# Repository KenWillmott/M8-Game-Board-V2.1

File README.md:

# M8-Game-Board-V2.1
Audio Video Joystick card for M8 bus

This board replaces the first game board, which was not fully working or fully M8 compatible.

It has a TMS9918A video processor with composite video output, stereo sound output from a Philips SAA1099 IC, and one Atari style joystick port. The sound IC and joystick are interfaced via an MC6821 PIA.

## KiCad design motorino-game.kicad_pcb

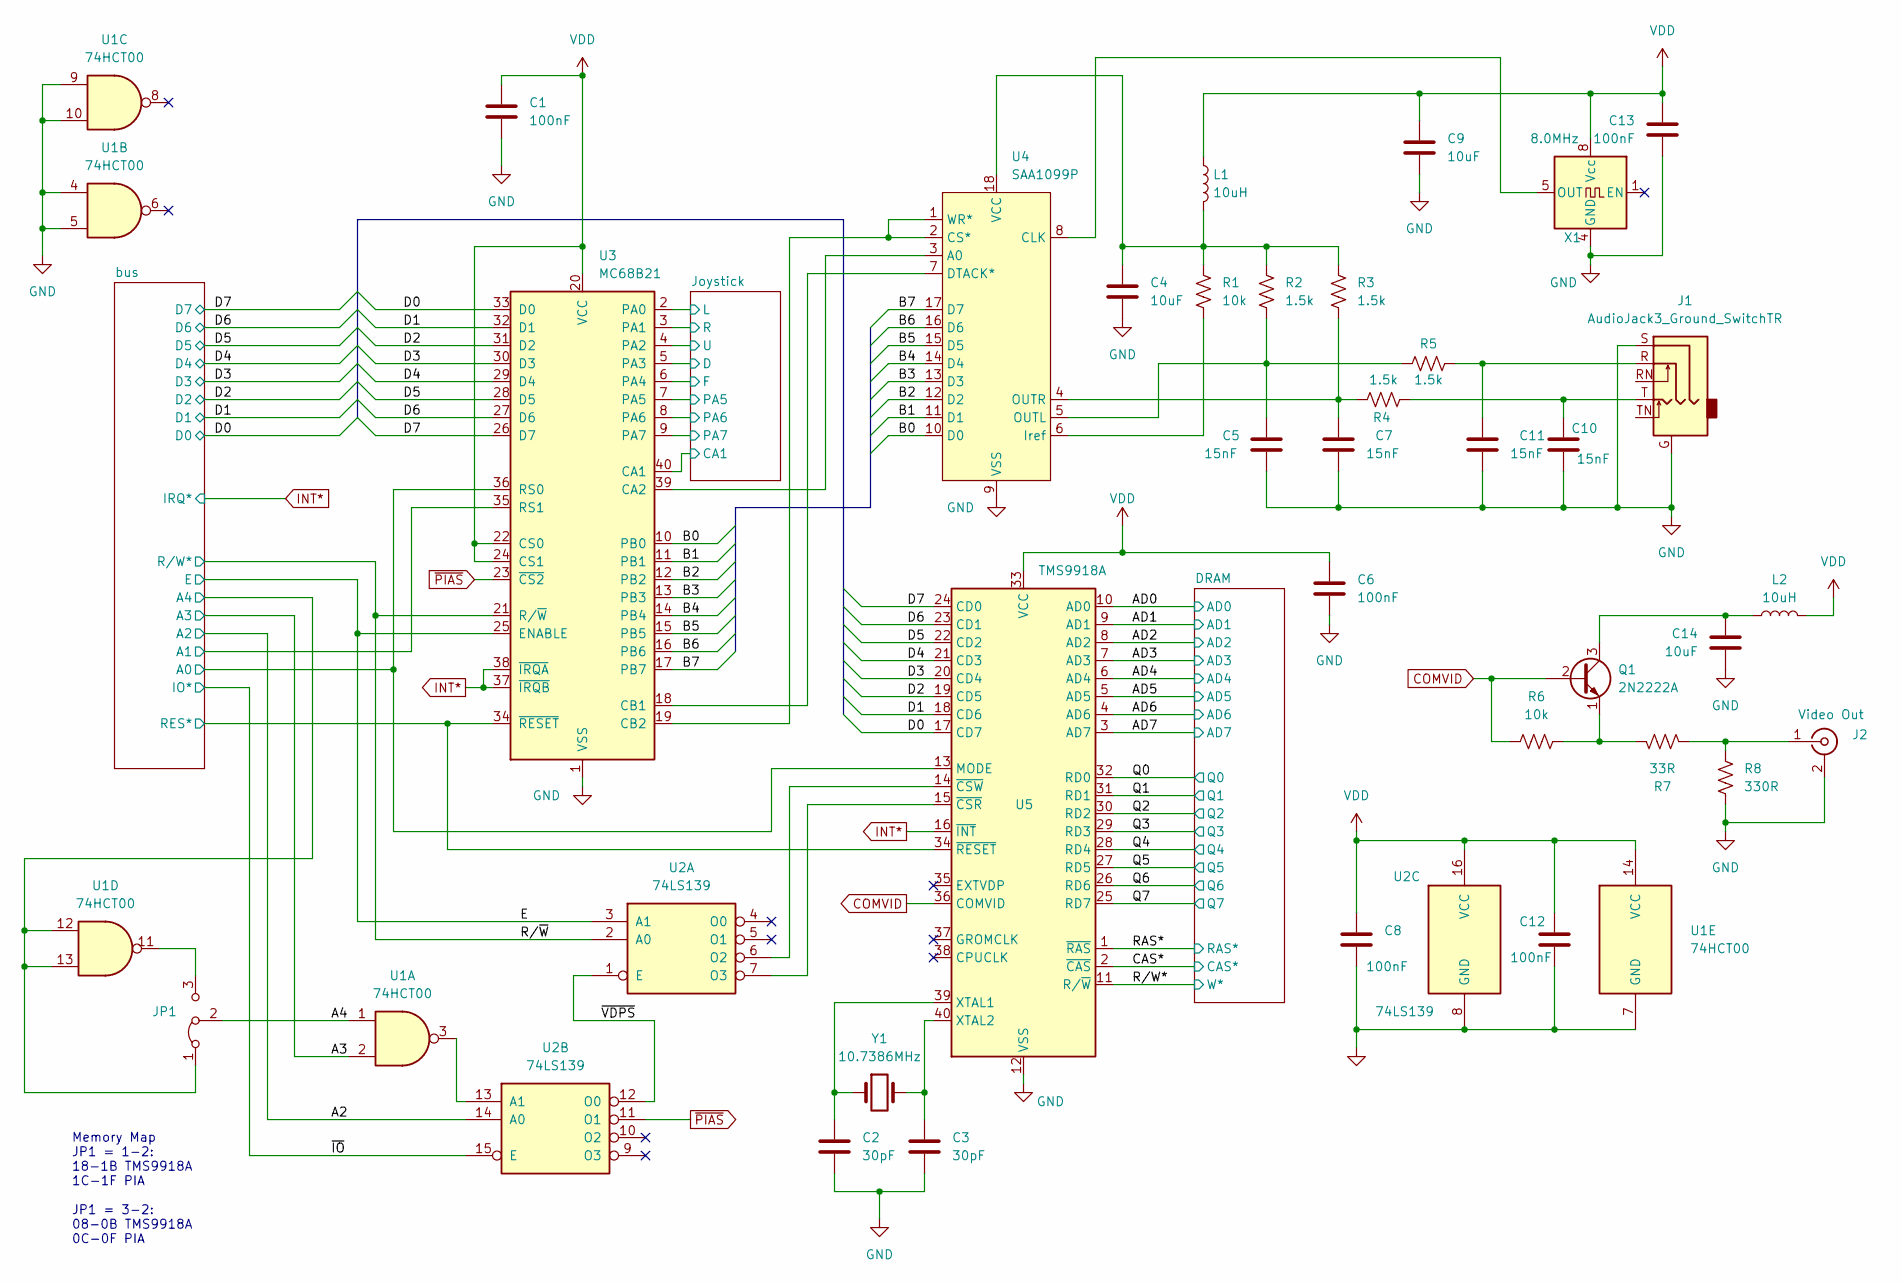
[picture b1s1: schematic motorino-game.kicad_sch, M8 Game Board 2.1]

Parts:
C1, C6, C8, C12, C13: 100nF; C_Disc_D5.0mm_W2.5mm_P5.00mm
C2, C3: 30pF; C_Disc_D5.0mm_W2.5mm_P5.00mm
C4, C9, C14: 10uF; C_Disc_D5.0mm_W2.5mm_P5.00mm
C5, C7, C10, C11: 15nF; C_Disc_D5.0mm_W2.5mm_P5.00mm
J1: AudioJack3_Ground_SwitchTR; Jack_3.5mm_CUI_SJ3-350113A-SMT_Horizontal
J2: Video Out; RCA jack
JP1: Jumper_3_Bridged12; PinHeader_1x03_P2.54mm_Vertical
L1, L2: 10uH; R_Axial_DIN0207_L6.3mm_D2.5mm_P10.16mm_Horizontal
Q1: 2N2222A; TO-92_Inline_Wide
R1, R6: 10k; R_Axial_DIN0207_L6.3mm_D2.5mm_P10.16mm_Horizontal
R2, R3, R4, R5: 1.5k; R_Axial_DIN0207_L6.3mm_D2.5mm_P10.16mm_Horizontal
R7: 33R; R_Axial_DIN0207_L6.3mm_D2.5mm_P10.16mm_Horizontal
R8: 330R; R_Axial_DIN0207_L6.3mm_D2.5mm_P10.16mm_Horizontal
U1: 74HCT00; DIP-14_W7.62mm_LongPads
U2: 74LS139; DIP-16_W7.62mm_LongPads
U3: MC68B21; DIP-40_W15.24mm
U4: SAA1099P; DIP-18_W7.62mm_LongPads
U5: TMS9918A; DIP-40_W15.24mm_LongPads
X1: 8.0MHz; Oscillator_DIP-8
Y1: 10.7386MHz; Crystal_HC49-U_Vertical

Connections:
/A2: U2.14 (A0); also elsewhere on the board
/A3: U1.2; also elsewhere on the board
/A4: JP1.2 (C), U1.1
/AD0: U5.10 (AD0); also elsewhere on the board
/AD1: U5.9 (AD1); also elsewhere on the board
/AD2: U5.8 (AD2); also elsewhere on the board
/AD3: U5.7 (AD3); also elsewhere on the board
/AD4: U5.6 (AD4); also elsewhere on the board
/AD5: U5.5 (AD5); also elsewhere on the board
/AD6: U5.4 (AD6); also elsewhere on the board
/AD7: U5.3 (AD7); also elsewhere on the board
/B0: U3.10 (PB0), U4.10 (D0)
/B1: U3.11 (PB1), U4.11 (D1)
/B2: U3.12 (PB2), U4.12 (D2)
/B3: U3.13 (PB3), U4.13 (D3)
/B4: U3.14 (PB4), U4.14 (D4)
/B5: U3.15 (PB5), U4.15 (D5)
/B6: U3.16 (PB6), U4.16 (D6)
/B7: U3.17 (PB7), U4.17 (D7)
/CAS*: U5.2 (~CAS); also elsewhere on the board
/D0: U3.33 (D0), U5.17 (CD7); also elsewhere on the board
/D1: U3.32 (D1), U5.18 (CD6); also elsewhere on the board
/D2: U3.31 (D2), U5.19 (CD5); also elsewhere on the board
/D3: U3.30 (D3), U5.20 (CD4); also elsewhere on the board
/D4: U3.29 (D4), U5.21 (CD3); also elsewhere on the board
/D5: U3.28 (D5), U5.22 (CD2); also elsewhere on the board
/D6: U3.27 (D6), U5.23 (CD1); also elsewhere on the board
/D7: U3.26 (D7), U5.24 (CD0); also elsewhere on the board
/E: U2.3 (A1), U3.25 (ENABLE); also elsewhere on the board
/Joystick/CA1: U3.40 (CA1); also elsewhere on the board
/Joystick/D: U3.5 (PA3); also elsewhere on the board
/Joystick/F: U3.6 (PA4); also elsewhere on the board
/Joystick/L: U3.2 (PA0); also elsewhere on the board
/Joystick/PA5: U3.7 (PA5); also elsewhere on the board
/Joystick/PA6: U3.8 (PA6); also elsewhere on the board
/Joystick/PA7: U3.9 (PA7); also elsewhere on the board
/Joystick/R: U3.3 (PA1); also elsewhere on the board
/Joystick/U: U3.4 (PA2); also elsewhere on the board
/Q0: U5.32 (RD0); also elsewhere on the board
/Q1: U5.31 (RD1); also elsewhere on the board
/Q2: U5.30 (RD2); also elsewhere on the board
/Q3: U5.29 (RD3); also elsewhere on the board
/Q4: U5.28 (RD4); also elsewhere on the board
/Q5: U5.27 (RD5); also elsewhere on the board
/Q6: U5.26 (RD6); also elsewhere on the board
/Q7: U5.25 (RD7); also elsewhere on the board
/RAS*: U5.1 (~RAS); also elsewhere on the board
/R/W*: U5.11 (R/~W); also elsewhere on the board
/R/~W: U2.2 (A0), U3.21 (R/~W); also elsewhere on the board
/bus/A0: U3.36 (RS0), U5.13 (MODE); also elsewhere on the board
/bus/A1: U3.35 (RS1); also elsewhere on the board
/bus/A4: JP1.1 (A), U1.12, U1.13; also elsewhere on the board
/bus/RES: U3.34 (~RESET), U5.34 (~RESET); also elsewhere on the board
/~IO: U2.15 (E); also elsewhere on the board
/~VDPS: U2.1 (E), U2.12 (O0)
COMVID: Q1.2 (B), R6.1, U5.36 (COMVID)
GND: C1.2, C2.2, C3.2, C4.2, C5.2, C6.2, C7.2, C8.2, C9.2, C10.2, C11.2, C12.2, C13.2, C14.2, J1.G, J1.S, J2.2 (Ext), R8.2, U1.4, U1.5, U1.7 (GND), U1.9, U1.10, U2.8 (GND), U3.1 (VSS), U4.9 (VSS), U5.12 (VSS), X1.4 (GND); also elsewhere on the board
INT*: U3.37 (~IRQB), U3.38 (~IRQA), U5.16 (~INT); also elsewhere on the board
unnamed: C10.1, J1.T, R4.1
unnamed: C11.1, J1.R, R5.1
unnamed: J2.1 (In), R7.1, R8.1
unnamed: JP1.3 (B), U1.11
unnamed: C14.1, L2.2, Q1.3 (C)
unnamed: Q1.1 (E), R6.2, R7.2
unnamed: U2.6 (O2), U5.14 (~CSW)
unnamed: U2.7 (O3), U5.15 (~CSR)
unnamed: U1.3, U2.13 (A1)
unnamed: U3.39 (CA2), U4.3 (A0)
unnamed: U3.18 (CB1), U4.7 (DTACK*)
unnamed: U3.19 (CB2), U4.1 (WR*), U4.2 (CS*)
unnamed: U4.8 (CLK), X1.5 (OUT)
unnamed: R1.2, U4.6 (Iref)
unnamed: C5.1, R2.2, R5.2, U4.5 (OUTL)
unnamed: C7.1, R3.2, R4.2, U4.4 (OUTR)
unnamed: C4.1, L1.2, R1.1, R2.1, R3.1, U4.18 (VCC)
unnamed: C2.1, U5.39 (XTAL1), Y1.1
unnamed: C3.1, U5.40 (XTAL2), Y1.2
VDD: C1.1, C6.1, C8.1, C9.1, C12.1, C13.1, L1.1, L2.1, U1.14 (VCC), U2.16 (VCC), U3.20 (VCC), U3.22 (CS0), U3.24 (CS1), U5.33 (VCC), X1.8 (Vcc); also elsewhere on the board
~PIAS: U2.11 (O1), U3.23 (~CS2)

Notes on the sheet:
Memory Map JP1 = 1-2: 18-1B TMS9918A 1C-1F PIA JP1 = 3-2: 08-0B TMS9918A 0C-0F PIA

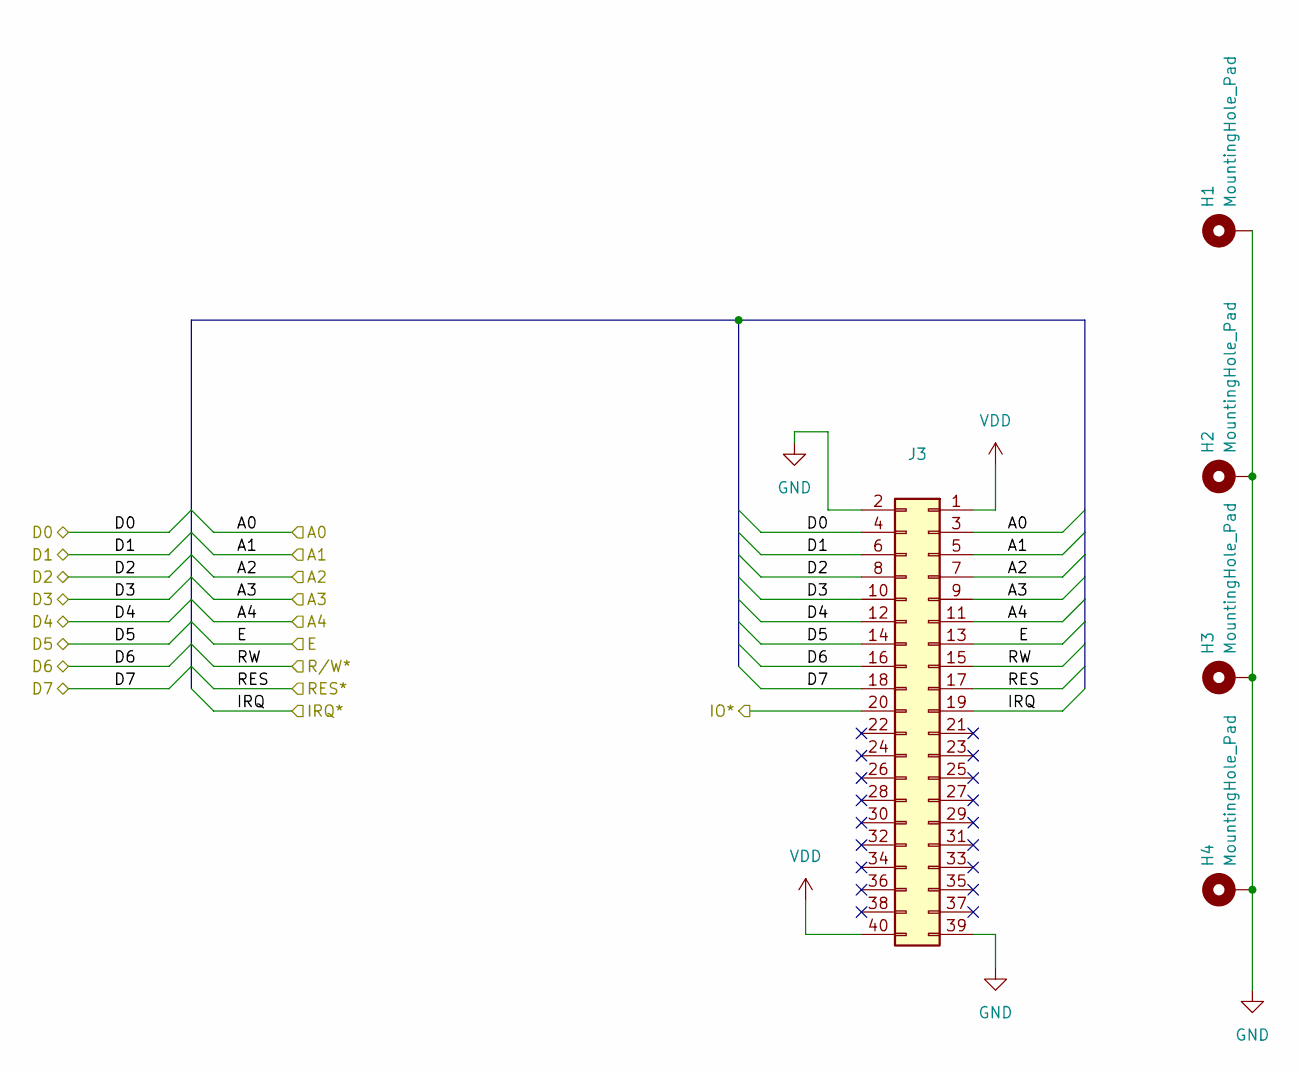
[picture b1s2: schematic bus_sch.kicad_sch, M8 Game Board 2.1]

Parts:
H1, H2, H3, H4: MountingHole_Pad; MountingHole_3.2mm_M3_Pad
J3: Conn_02x20_Odd_Even; PinHeader_2x20_P2.54mm_Vertical

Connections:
/A2: J3.7; also elsewhere on the board
/A3: J3.9; also elsewhere on the board
/D0: J3.4; also elsewhere on the board
/D1: J3.6; also elsewhere on the board
/D2: J3.8; also elsewhere on the board
/D3: J3.10; also elsewhere on the board
/D4: J3.12; also elsewhere on the board
/D5: J3.14; also elsewhere on the board
/D6: J3.16; also elsewhere on the board
/D7: J3.18; also elsewhere on the board
/E: J3.13; also elsewhere on the board
/R/~W: J3.15; also elsewhere on the board
/bus/A0: J3.3; also elsewhere on the board
/bus/A1: J3.5; also elsewhere on the board
/bus/A4: J3.11; also elsewhere on the board
/bus/RES: J3.17; also elsewhere on the board
/~IO: J3.20; also elsewhere on the board
GND: H1.1, H2.1, H3.1, H4.1, J3.2, J3.39; also elsewhere on the board
INT*: J3.19; also elsewhere on the board
VDD: J3.1, J3.40; also elsewhere on the board

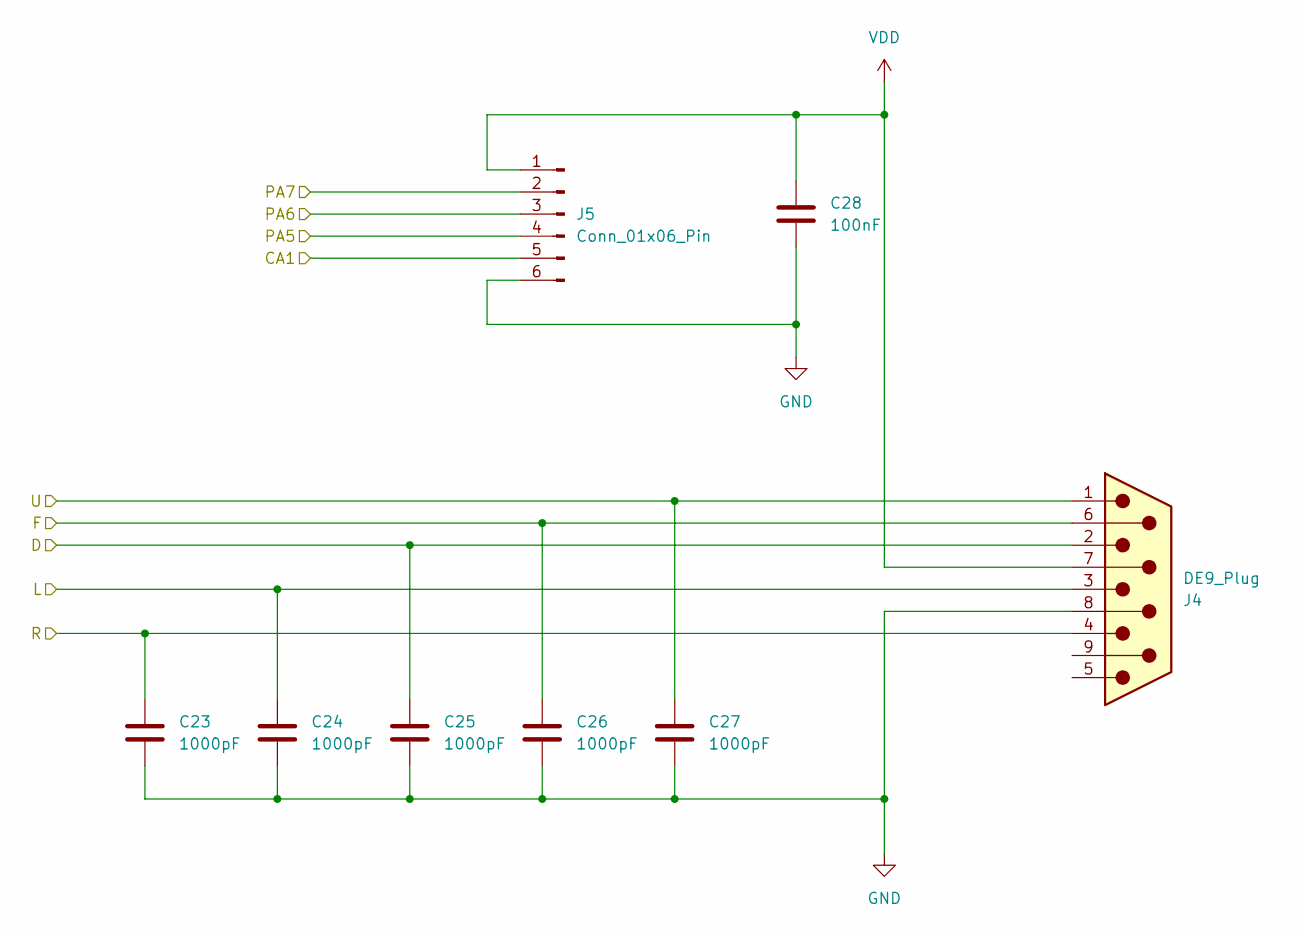
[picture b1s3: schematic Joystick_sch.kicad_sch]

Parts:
C23, C24, C25, C26, C27: 1000pF; C_Disc_D5.0mm_W2.5mm_P5.00mm
C28: 100nF; C_Disc_D5.0mm_W2.5mm_P5.00mm
J4: DE9_Plug; DSUB-9_Male_Horizontal_P2.77x2.84mm_EdgePinOffset9.90mm_Hou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
J5: Conn_01x06_Pin; PinHeader_1x06_P2.54mm_Vertical

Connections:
/Joystick/CA1: J5.5; also elsewhere on the board
/Joystick/D: C25.1, J4.2; also elsewhere on the board
/Joystick/F: C26.1, J4.6; also elsewhere on the board
/Joystick/L: C24.1, J4.3; also elsewhere on the board
/Joystick/PA5: J5.4; also elsewhere on the board
/Joystick/PA6: J5.3; also elsewhere on the board
/Joystick/PA7: J5.2; also elsewhere on the board
/Joystick/R: C23.1, J4.4; also elsewhere on the board
/Joystick/U: C27.1, J4.1; also elsewhere on the board
GND: C23.2, C24.2, C25.2, C26.2, C27.2, C28.2, J4.8, J5.6; also elsewhere on the board
VDD: C28.1, J4.7, J5.1; also elsewhere on the board

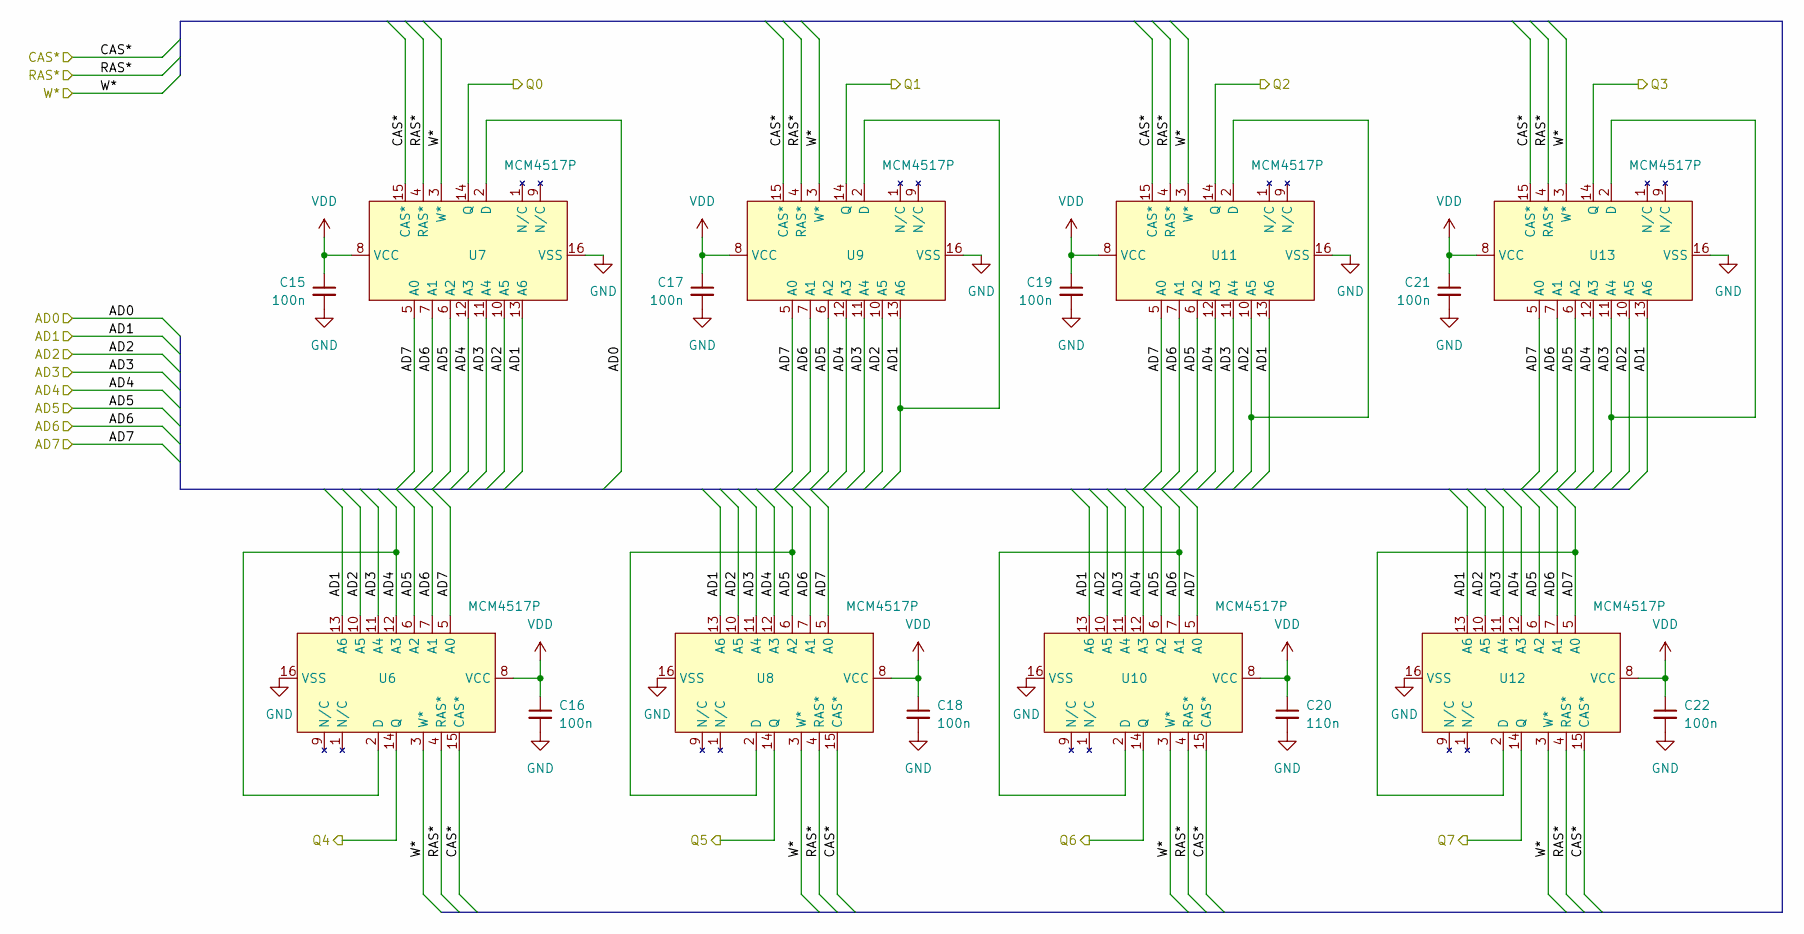
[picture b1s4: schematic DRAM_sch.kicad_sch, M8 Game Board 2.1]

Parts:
C15, C16, C17, C18, C19, C21, C22: 100n; C_Disc_D5.0mm_W2.5mm_P5.00mm
C20: 110n; C_Disc_D5.0mm_W2.5mm_P5.00mm
U6, U7, U8, U9, U10, U11, U12, U13: MCM4517P; DIP-16_W7.62mm_LongPads

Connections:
/AD0: U7.2 (D); also elsewhere on the board
/AD1: U6.13 (A6), U7.13 (A6), U8.13 (A6), U9.2 (D), U9.13 (A6), U10.13 (A6), U11.13 (A6), U12.13 (A6), U13.13 (A6); also elsewhere on the board
/AD2: U6.10 (A5), U7.10 (A5), U8.10 (A5), U9.10 (A5), U10.10 (A5), U11.2 (D), U11.10 (A5), U12.10 (A5), U13.10 (A5); also elsewhere on the board
/AD3: U6.11 (A4), U7.11 (A4), U8.11 (A4), U9.11 (A4), U10.11 (A4), U11.11 (A4), U12.11 (A4), U13.2 (D), U13.11 (A4); also elsewhere on the board
/AD4: U6.2 (D), U6.12 (A3), U7.12 (A3), U8.12 (A3), U9.12 (A3), U10.12 (A3), U11.12 (A3), U12.12 (A3), U13.12 (A3); also elsewhere on the board
/AD5: U6.6 (A2), U7.6 (A2), U8.2 (D), U8.6 (A2), U9.6 (A2), U10.6 (A2), U11.6 (A2), U12.6 (A2), U13.6 (A2); also elsewhere on the board
/AD6: U6.7 (A1), U7.7 (A1), U8.7 (A1), U9.7 (A1), U10.2 (D), U10.7 (A1), U11.7 (A1), U12.7 (A1), U13.7 (A1); also elsewhere on the board
/AD7: U6.5 (A0), U7.5 (A0), U8.5 (A0), U9.5 (A0), U10.5 (A0), U11.5 (A0), U12.2 (D), U12.5 (A0), U13.5 (A0); also elsewhere on the board
/CAS*: U6.15 (CAS*), U7.15 (CAS*), U8.15 (CAS*), U9.15 (CAS*), U10.15 (CAS*), U11.15 (CAS*), U12.15 (CAS*), U13.15 (CAS*); also elsewhere on the board
/Q0: U7.14 (Q); also elsewhere on the board
/Q1: U9.14 (Q); also elsewhere on the board
/Q2: U11.14 (Q); also elsewhere on the board
/Q3: U13.14 (Q); also elsewhere on the board
/Q4: U6.14 (Q); also elsewhere on the board
/Q5: U8.14 (Q); also elsewhere on the board
/Q6: U10.14 (Q); also elsewhere on the board
/Q7: U12.14 (Q); also elsewhere on the board
/RAS*: U6.4 (RAS*), U7.4 (RAS*), U8.4 (RAS*), U9.4 (RAS*), U10.4 (RAS*), U11.4 (RAS*), U12.4 (RAS*), U13.4 (RAS*); also elsewhere on the board
/R/W*: U6.3 (W*), U7.3 (W*), U8.3 (W*), U9.3 (W*), U10.3 (W*), U11.3 (W*), U12.3 (W*), U13.3 (W*); also elsewhere on the board
GND: C15.2, C16.2, C17.2, C18.2, C19.2, C20.2, C21.2, C22.2, U6.16 (VSS), U7.16 (VSS), U8.16 (VSS), U9.16 (VSS), U10.16 (VSS), U11.16 (VSS), U12.16 (VSS), U13.16 (VSS); also elsewhere on the board
VDD: C15.1, C16.1, C17.1, C18.1, C19.1, C20.1, C21.1, C22.1, U6.8 (VCC), U7.8 (VCC), U8.8 (VCC), U9.8 (VCC), U10.8 (VCC), U11.8 (VCC), U12.8 (VCC), U13.8 (VCC); also elsewhere on the board

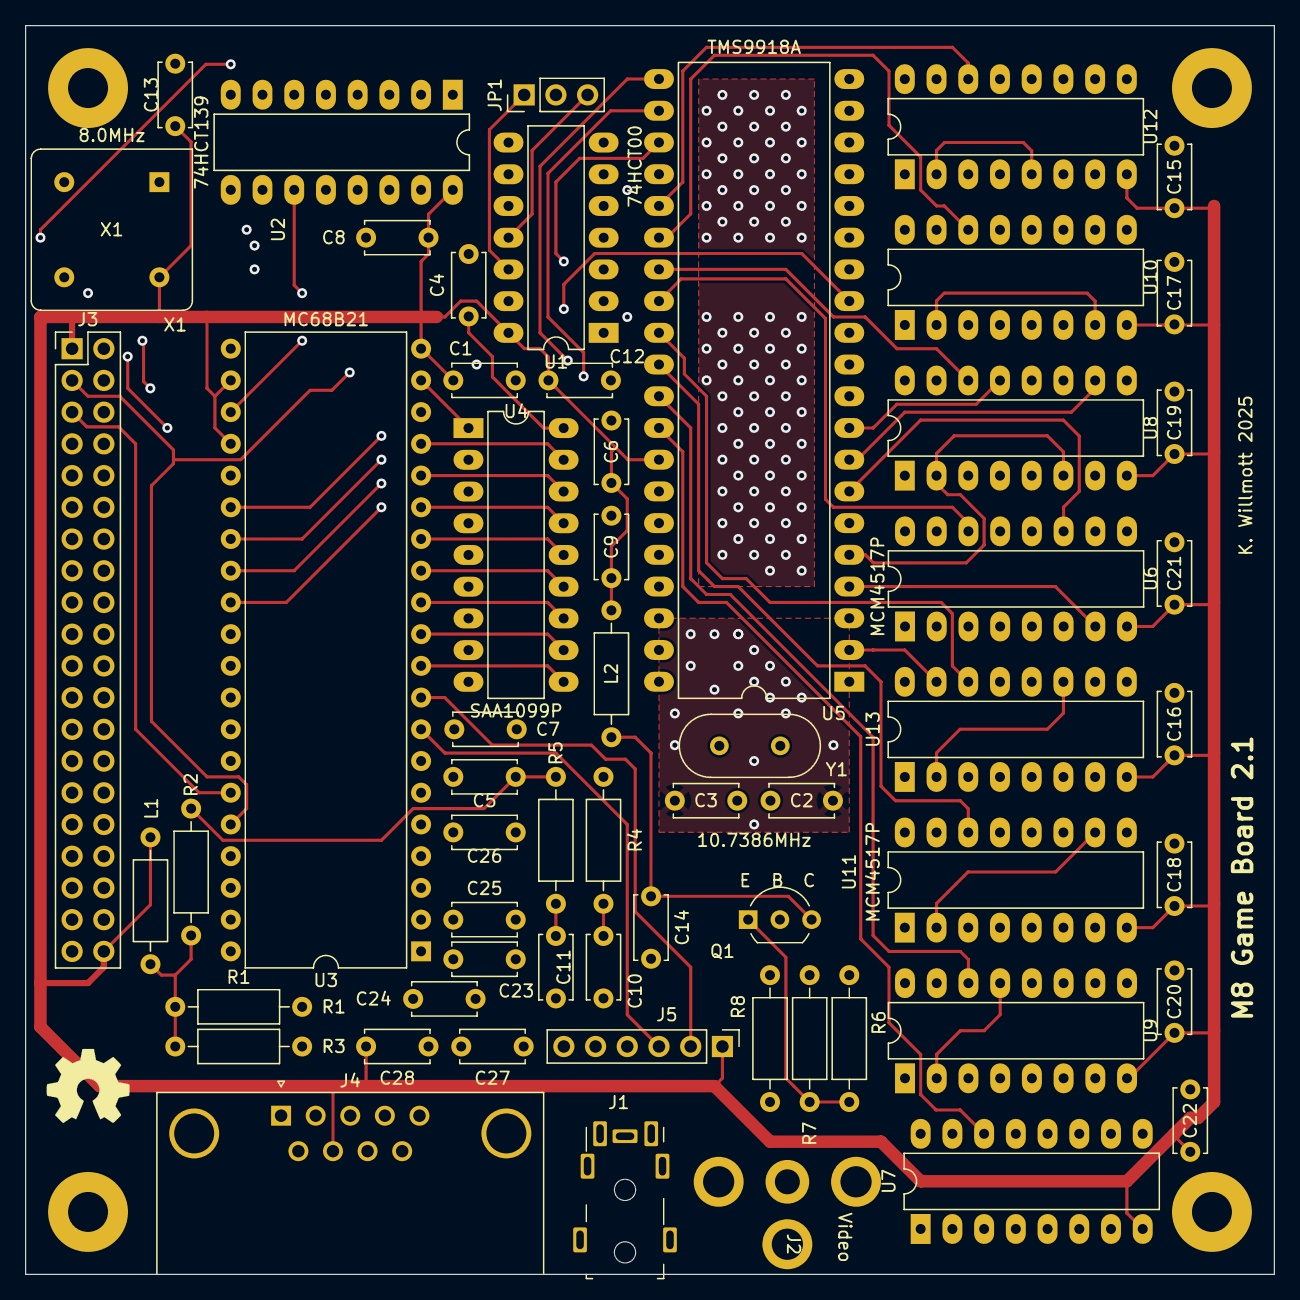
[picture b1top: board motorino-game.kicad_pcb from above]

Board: 4 copper layers, 100.0 x 100.0 mm, 64 parts (0 on the bottom side), 79 nets.
